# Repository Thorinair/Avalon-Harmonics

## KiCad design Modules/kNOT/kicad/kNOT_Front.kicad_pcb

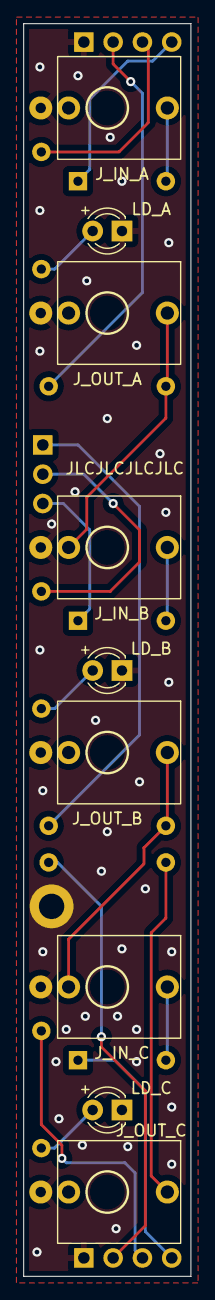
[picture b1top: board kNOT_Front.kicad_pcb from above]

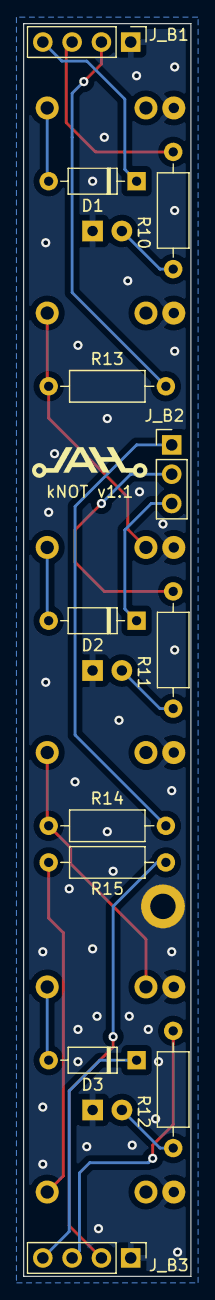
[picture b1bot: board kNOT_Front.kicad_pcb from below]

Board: 2 copper layers, 14.5 x 108.6 mm, 21 parts (12 on the bottom side), 19 nets.

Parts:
D1, D2, D3: 1N4148; D_DO-35_SOD27_P7.62mm_Horizontal
J_B1, J_B3: Conn_01x04_Female; PinHeader_1x04_P2.54mm_Vertical
J_B2: Conn_01x03_Female; PinHeader_1x03_P2.54mm_Vertical
J_IN_A: PJ301M-12
J_IN_B: PJ301M-12
J_IN_C: PJ301M-12
J_OUT_A: PJ301M-12
J_OUT_B: PJ301M-12
J_OUT_C: PJ301M-12
LD_A: LED; LED_D3.0mm_FlatTop
LD_B: LED; LED_D3.0mm_FlatTop
LD_C: LED; LED_D3.0mm_FlatTop
R10, R11, R12: 10k; R_Axial_DIN0207_L6.3mm_D2.5mm_P10.16mm_Horizontal
R13, R14, R15: 1k; R_Axial_DIN0207_L6.3mm_D2.5mm_P10.16mm_Horizontal

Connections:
/NORM_A: J_IN_B.SW, J_OUT_A.SIG, R13.1
/NORM_B: J_IN_C.SW, J_OUT_B.SIG, R14.1
GND: J_B1.1, J_B3.1, J_IN_A.GND, J_IN_B.GND, J_IN_C.GND, J_OUT_A.GND, J_OUT_B.GND, J_OUT_C.GND, LD_A.1 (K), LD_B.1 (K), LD_C.1 (K)
unnamed: D1.2 (A), J_IN_A.SIG
unnamed: D1.1 (K), J_B1.4
unnamed: D2.2 (A), J_IN_B.SIG
unnamed: D2.1 (K), J_B2.3
unnamed: D3.2 (A), J_IN_C.SIG
unnamed: D3.1 (K), J_B3.4
unnamed: J_B1.2, R13.2
unnamed: J_B1.3, R10.1
unnamed: J_B2.1, R14.2
unnamed: J_B2.2, R11.1
unnamed: J_B3.2, R15.2
unnamed: J_B3.3, R12.1
unnamed: J_OUT_C.SIG, R15.1
unnamed: LD_A.2 (A), R10.2
unnamed: LD_B.2 (A), R11.2
unnamed: LD_C.2 (A), R12.2

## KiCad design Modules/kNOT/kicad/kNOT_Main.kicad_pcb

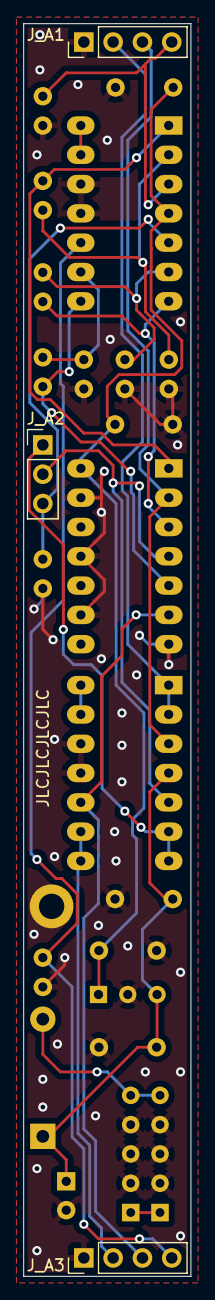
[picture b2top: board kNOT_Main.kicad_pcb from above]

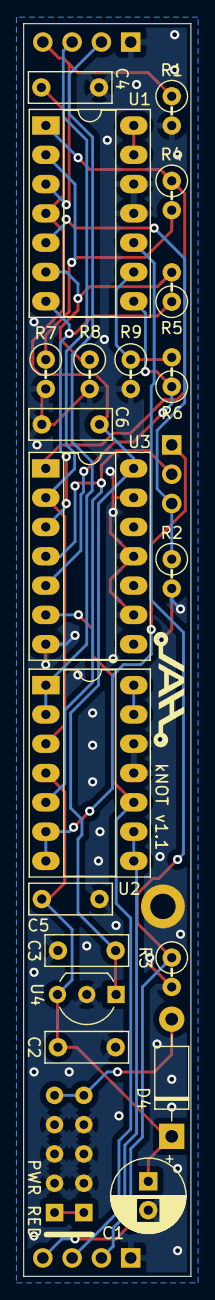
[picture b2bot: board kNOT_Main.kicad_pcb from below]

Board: 2 copper layers, 14.5 x 108.6 mm, 24 parts (21 on the bottom side), 21 nets.

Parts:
C1: 47uF; CP_Radial_D6.3mm_P2.50mm
C2, C3, C4, C5, C6: 0.1uF; C_Disc_D7.0mm_W2.5mm_P5.00mm
D4: 1N4001; D_DO-41_SOD81_P10.16mm_Horizontal
J_A1, J_A3: Conn_01x04_Male; PinHeader_1x04_P2.54mm_Vertical
J_A2: Conn_01x03_Male; PinHeader_1x03_P2.54mm_Vertical
PWR1: PWR_10_Pin; Eurorack Power 10 Pin
R1, R2, R3, R4, R5, R6: 100k; R_Axial_DIN0207_L6.3mm_D2.5mm_P2.54mm_Vertical
R7, R8, R9: 47k; R_Axial_DIN0207_L6.3mm_D2.5mm_P2.54mm_Vertical
U1, U2: LM324; DIP-14_W7.62mm_Socket_LongPads
U3: 74HC04; DIP-14_W7.62mm_Socket_LongPads
U4: 78L05; TO-92_Inline_Wide

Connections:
+5V: C3.1, C4.1, C6.1, U1.4 (V+), U3.14 (VCC), U4.1 (VO)
+12V: C1.1, C2.1, C5.1, D4.1 (K), U2.4 (V+), U4.3 (VI)
/LED_A: J_A1.3, U2.3 (+), U3.2
/LED_B: J_A2.2, U2.5 (+), U3.4
/LED_C: J_A3.3, U2.10 (+), U3.6
/OUT_A: J_A1.2, U2.1, U2.2 (-)
/OUT_B: J_A2.1, U2.6 (-), U2.7
/OUT_C: J_A3.2, U2.8, U2.9 (-)
GND: C1.2, C2.2, C3.2, C4.2, C5.2, C6.2, J_A1.1, J_A3.1, PWR1.2 (GND), R1.2, R2.2, R3.2, R7.2, R8.2, R9.2, U1.11 (V-), U1.12 (+), U2.11 (V-), U2.12 (+), U3.7 (GND), U3.9, U3.11, U3.13, U4.2 (GND)
unnamed: D4.2 (A), PWR1.1 (+12V)
unnamed: J_A1.4, R1.1, U1.3 (+)
unnamed: J_A2.3, R2.1, U1.5 (+)
unnamed: J_A3.4, R3.1, U1.10 (+)
unnamed: R4.1, U1.1, U3.1
unnamed: R5.1, U1.7, U3.3
unnamed: R6.1, U1.8, U3.5
unnamed: R4.2, R7.1, U1.2 (-)
unnamed: R5.2, R8.1, U1.6 (-)
unnamed: R6.2, R9.1, U1.9 (-)
unnamed: U1.13 (-), U1.14
unnamed: U2.13 (-), U2.14
